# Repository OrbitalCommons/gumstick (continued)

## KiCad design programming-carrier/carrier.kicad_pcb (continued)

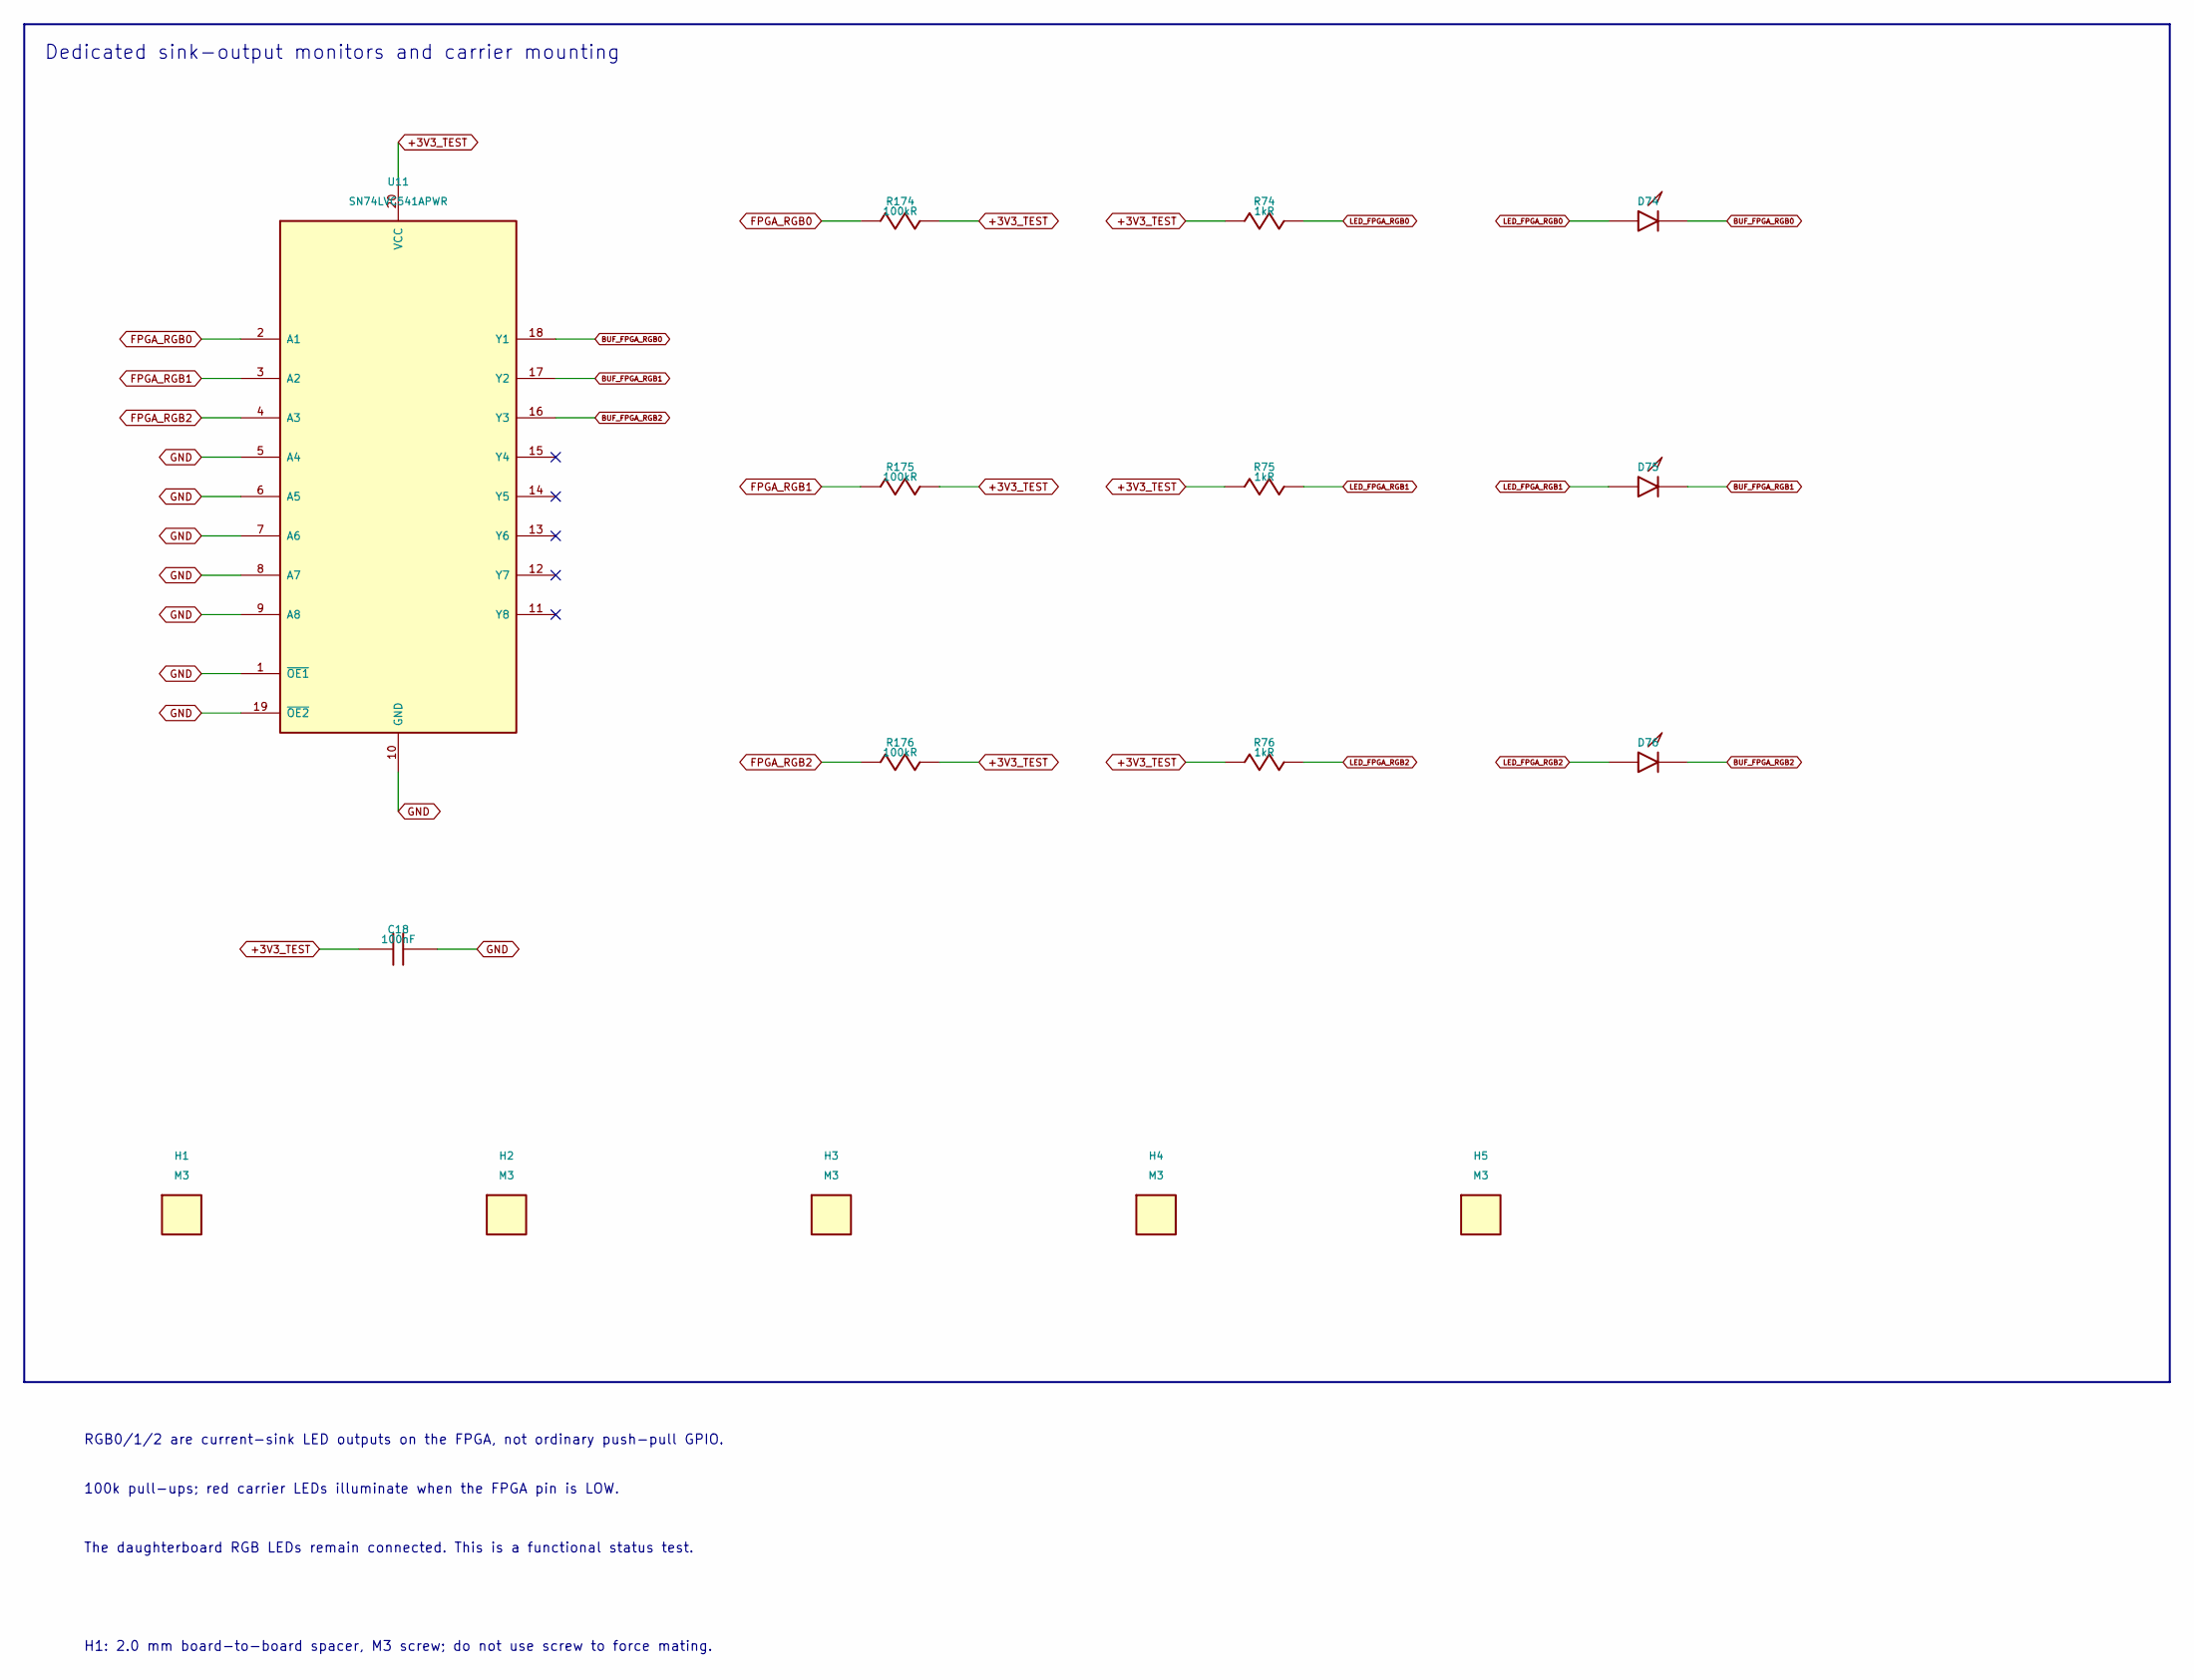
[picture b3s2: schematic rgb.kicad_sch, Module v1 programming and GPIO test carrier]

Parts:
C18: 100nF; C_0603_1608Metric; MPN CC0603KRX7R9BB104; LCSC C14663
D74, D75, D76: RED; LED_0603_1608Metric; MPN KT-0603R; LCSC C2286
H1, H2, H3, H4, H5: M3; MountingHole_3.2mm_M3; MPN M3
R74, R75, R76: 1kR; R_0603_1608Metric; MPN 0603WAF1001T5E; LCSC C21190
R174, R175, R176: 100kR; R_0603_1608Metric; MPN 0603WAF1003T5E; LCSC C25803
U11: SN74LVC541APWR; TSSOP-20_4.4x6.5mm_P0.65mm; MPN SN74LVC541APWR; LCSC C113281

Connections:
+3V3_TEST: C18.1, R74.1, R75.1, R76.1, R174.2, R175.2, R176.2, U11.20 (VCC); also elsewhere on the board
BUF_FPGA_RGB0: D74.1, U11.18 (Y1)
BUF_FPGA_RGB1: D75.1, U11.17 (Y2)
BUF_FPGA_RGB2: D76.1, U11.16 (Y3)
FPGA_RGB0: R174.1, U11.2 (A1); also elsewhere on the board
FPGA_RGB1: R175.1, U11.3 (A2); also elsewhere on the board
FPGA_RGB2: R176.1, U11.4 (A3); also elsewhere on the board
GND: C18.2, U11.1 (~OE1), U11.5 (A4), U11.6 (A5), U11.7 (A6), U11.8 (A7), U11.9 (A8), U11.10 (GND), U11.19 (~OE2); also elsewhere on the board
LED_FPGA_RGB0: D74.2, R74.2
LED_FPGA_RGB1: D75.2, R75.2
LED_FPGA_RGB2: D76.2, R76.2

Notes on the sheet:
Dedicated sink-output monitors and carrier mounting
RGB0/1/2 are current-sink LED outputs on the FPGA, not ordinary push-pull GPIO.
100k pull-ups; red carrier LEDs illuminate when the FPGA pin is LOW.
The daughterboard RGB LEDs remain connected. This is a functional status test.
H1: 2.0 mm board-to-board spacer, M3 screw; do not use screw to force mating.

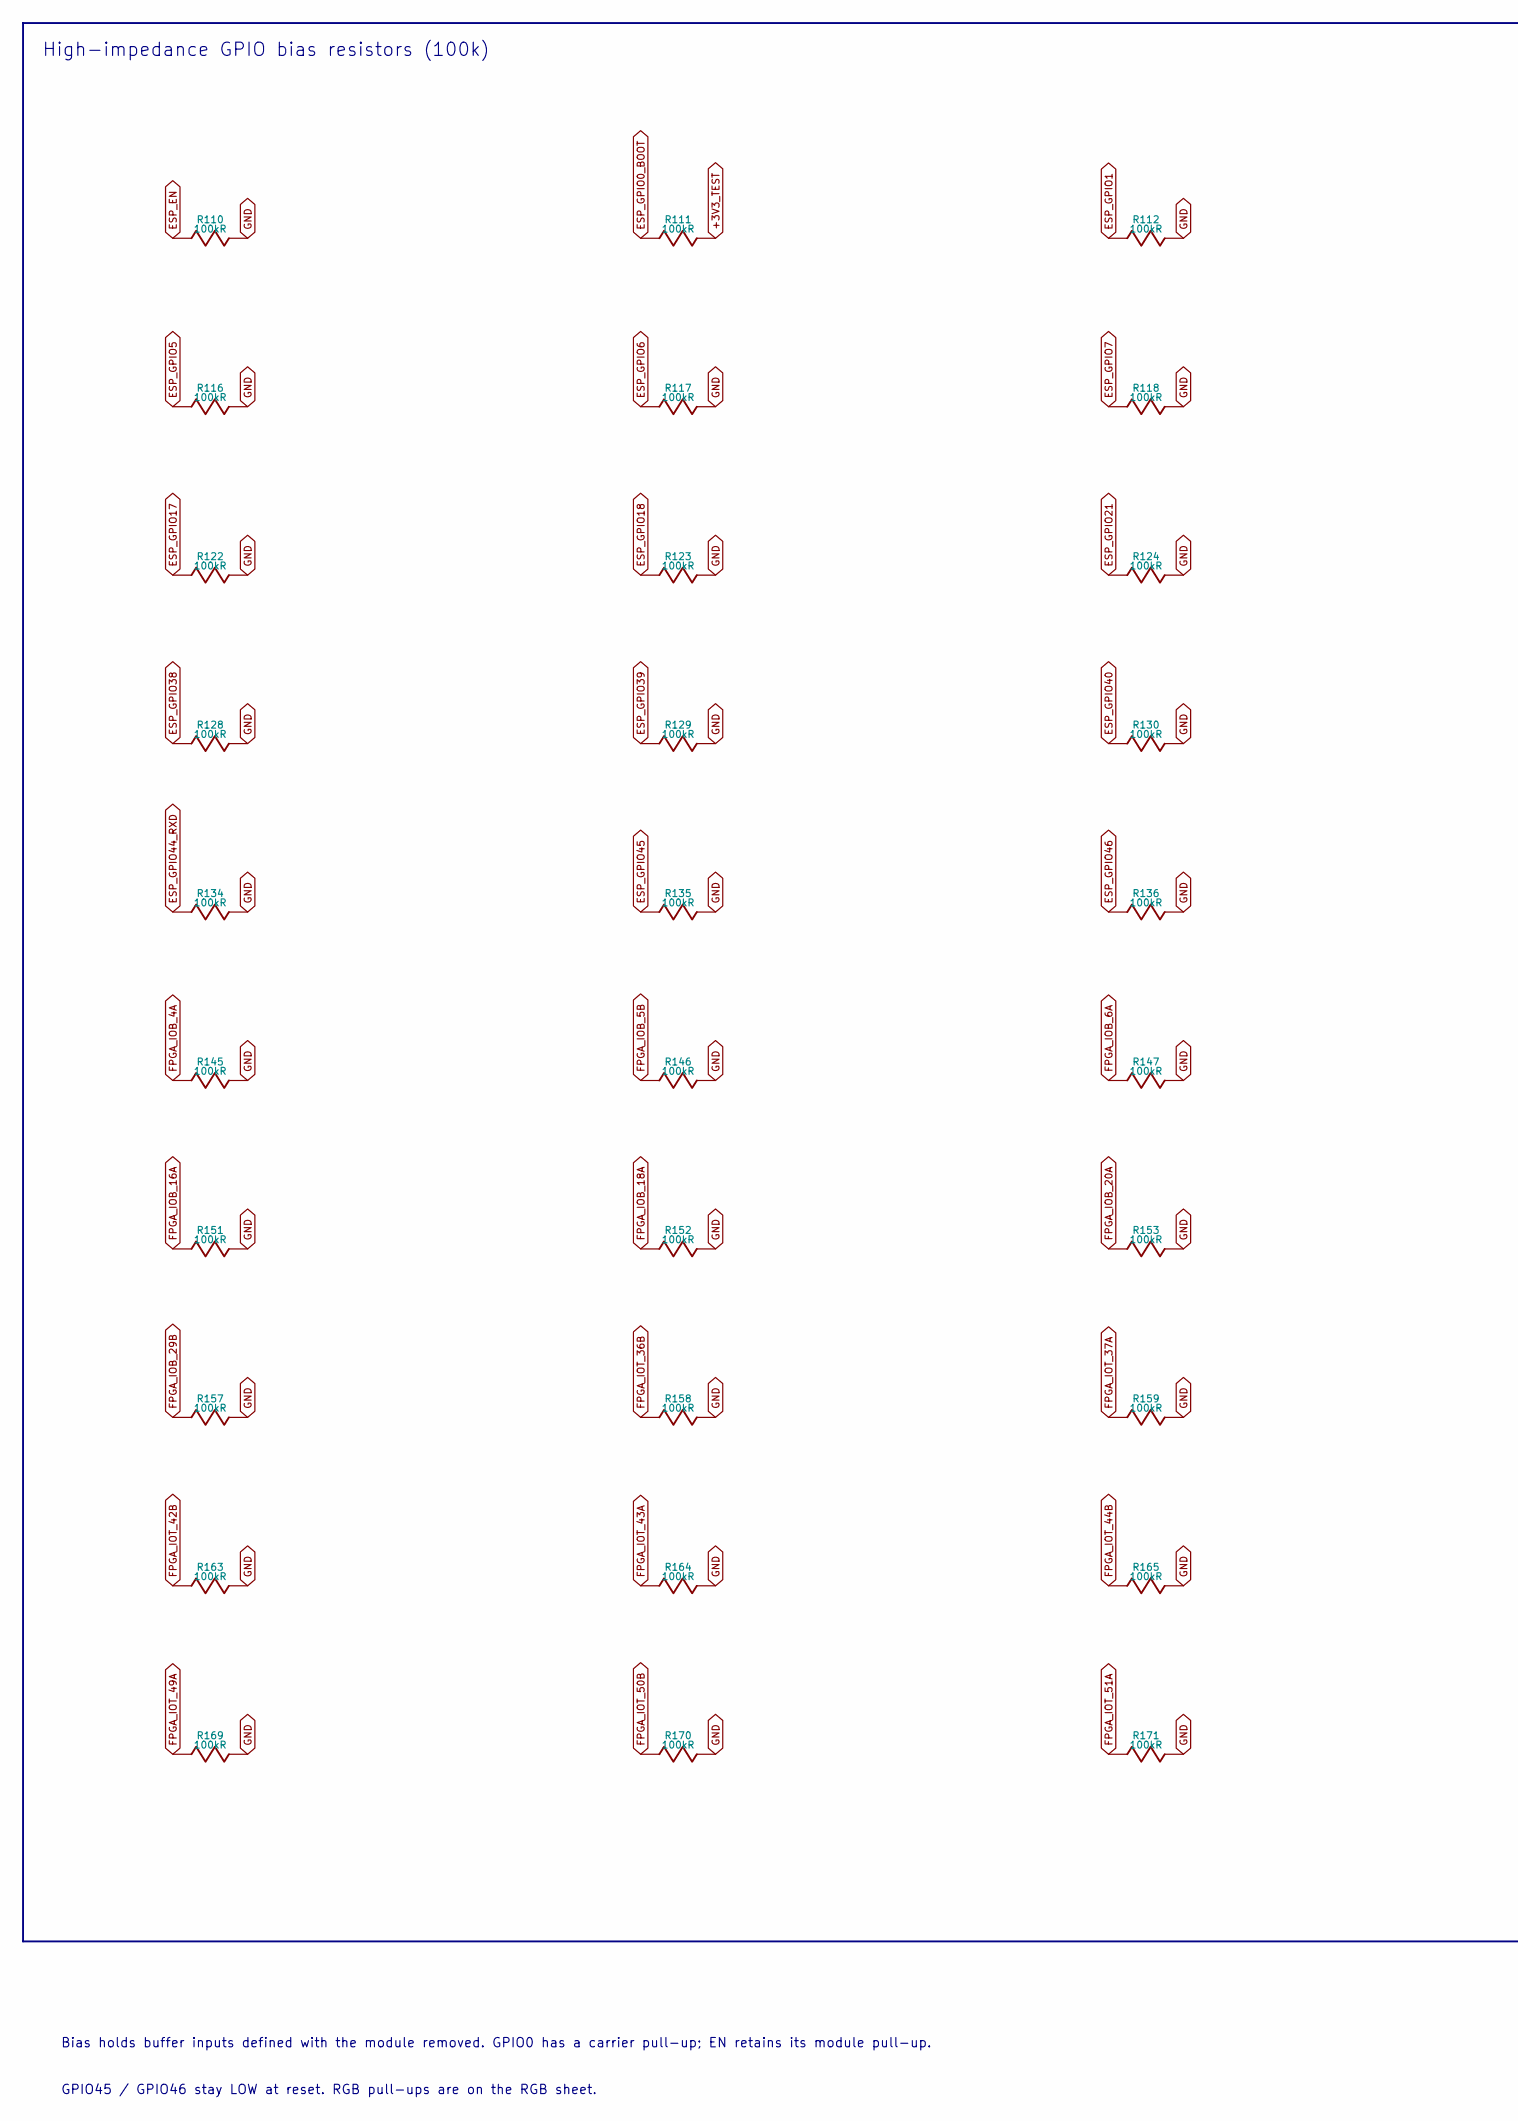
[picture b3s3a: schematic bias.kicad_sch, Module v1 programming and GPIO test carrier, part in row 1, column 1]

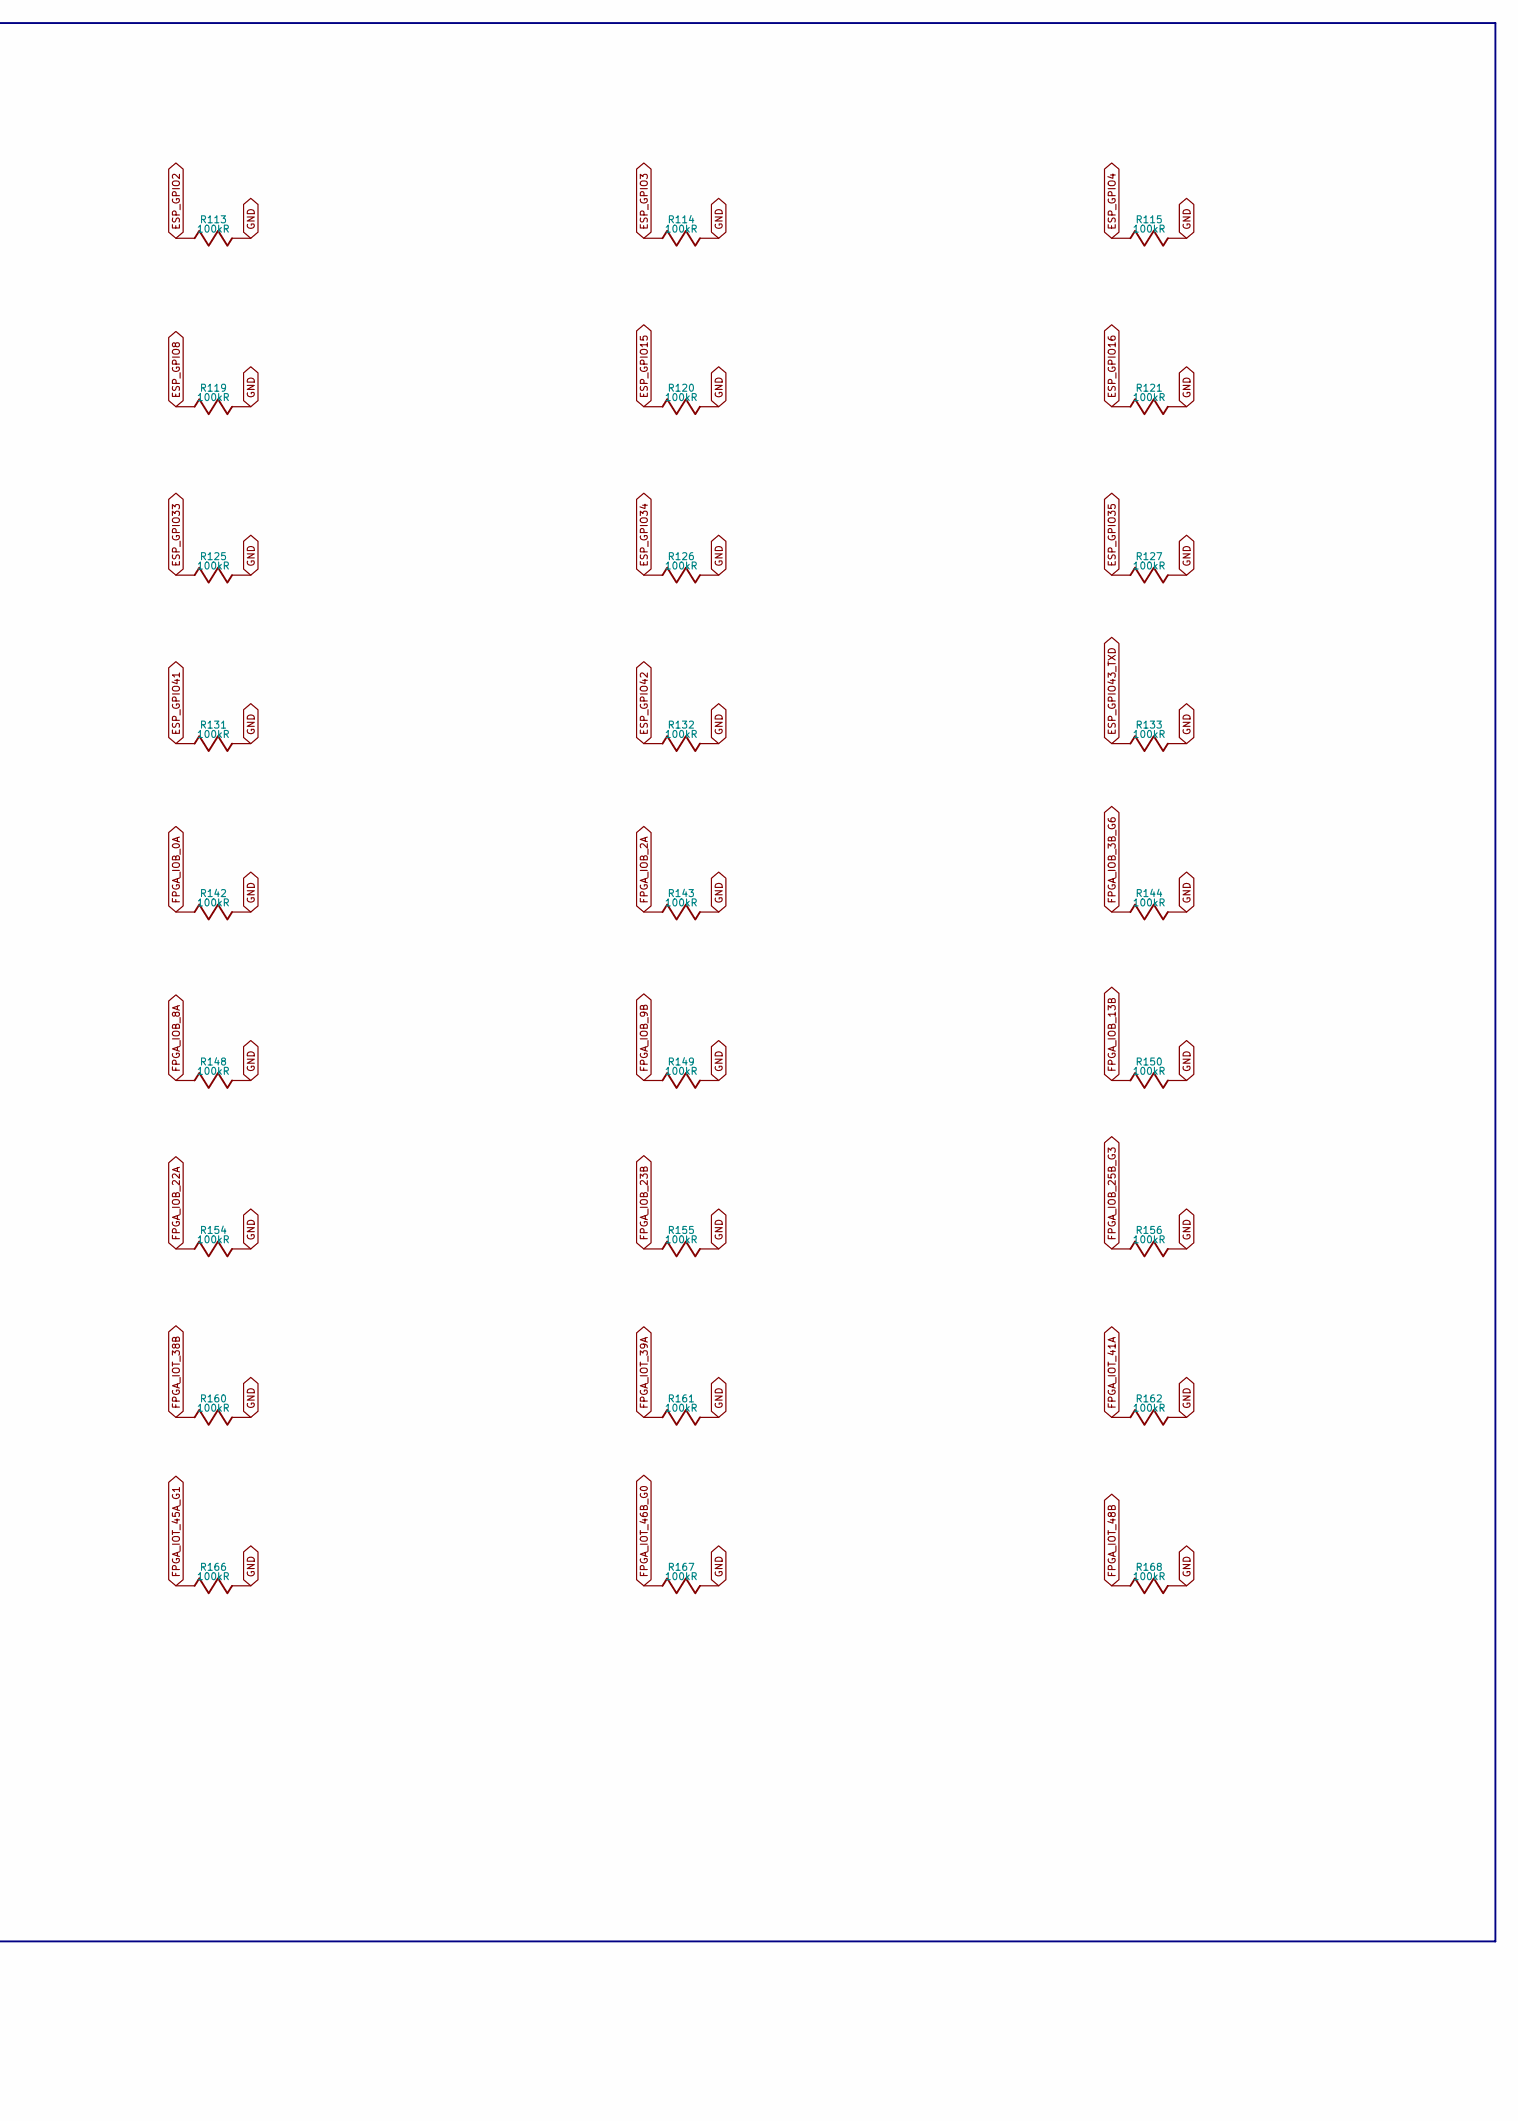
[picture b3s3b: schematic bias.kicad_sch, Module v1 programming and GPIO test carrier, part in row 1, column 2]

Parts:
R110, R111, R112, R113, R114, R115, R116, R117, R118, R119, R120, R121, R122, R123, R124, R125, R126, R127, R128, R129, R130, R131, R132, R133, R134, R135, R136, R142, R143, R144, R145, R146, R147, R148, R149, R150, R151, R152, R153, R154, R155, R156, R157, R158, R159, R160, R161, R162, R163, R164, R165, R166, R167, R168, R169, R170, R171: 100kR; R_0603_1608Metric; MPN 0603WAF1003T5E; LCSC C25803

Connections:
+3V3_TEST: R111.2; also elsewhere on the board
ESP_EN: R110.1; also elsewhere on the board
ESP_GPIO0_BOOT: R111.1; also elsewhere on the board
ESP_GPIO1: R112.1; also elsewhere on the board
ESP_GPIO2: R113.1; also elsewhere on the board
ESP_GPIO3: R114.1; also elsewhere on the board
ESP_GPIO4: R115.1; also elsewhere on the board
ESP_GPIO5: R116.1; also elsewhere on the board
ESP_GPIO6: R117.1; also elsewhere on the board
ESP_GPIO7: R118.1; also elsewhere on the board
ESP_GPIO8: R119.1; also elsewhere on the board
ESP_GPIO15: R120.1; also elsewhere on the board
ESP_GPIO16: R121.1; also elsewhere on the board
ESP_GPIO17: R122.1; also elsewhere on the board
ESP_GPIO18: R123.1; also elsewhere on the board
ESP_GPIO21: R124.1; also elsewhere on the board
ESP_GPIO33: R125.1; also elsewhere on the board
ESP_GPIO34: R126.1; also elsewhere on the board
ESP_GPIO35: R127.1; also elsewhere on the board
ESP_GPIO38: R128.1; also elsewhere on the board
ESP_GPIO39: R129.1; also elsewhere on the board
ESP_GPIO40: R130.1; also elsewhere on the board
ESP_GPIO41: R131.1; also elsewhere on the board
ESP_GPIO42: R132.1; also elsewhere on the board
ESP_GPIO43_TXD: R133.1; also elsewhere on the board
ESP_GPIO44_RXD: R134.1; also elsewhere on the board
ESP_GPIO45: R135.1; also elsewhere on the board
ESP_GPIO46: R136.1; also elsewhere on the board
FPGA_IOB_0A: R142.1; also elsewhere on the board
FPGA_IOB_2A: R143.1; also elsewhere on the board
FPGA_IOB_3B_G6: R144.1; also elsewhere on the board
FPGA_IOB_4A: R145.1; also elsewhere on the board
FPGA_IOB_5B: R146.1; also elsewhere on the board
FPGA_IOB_6A: R147.1; also elsewhere on the board
FPGA_IOB_8A: R148.1; also elsewhere on the board
FPGA_IOB_9B: R149.1; also elsewhere on the board
FPGA_IOB_13B: R150.1; also elsewhere on the board
FPGA_IOB_16A: R151.1; also elsewhere on the board
FPGA_IOB_18A: R152.1; also elsewhere on the board
FPGA_IOB_20A: R153.1; also elsewhere on the board
FPGA_IOB_22A: R154.1; also elsewhere on the board
FPGA_IOB_23B: R155.1; also elsewhere on the board
FPGA_IOB_25B_G3: R156.1; also elsewhere on the board
FPGA_IOB_29B: R157.1; also elsewhere on the board
FPGA_IOT_36B: R158.1; also elsewhere on the board
FPGA_IOT_37A: R159.1; also elsewhere on the board
FPGA_IOT_38B: R160.1; also elsewhere on the board
FPGA_IOT_39A: R161.1; also elsewhere on the board
FPGA_IOT_41A: R162.1; also elsewhere on the board
FPGA_IOT_42B: R163.1; also elsewhere on the board
FPGA_IOT_43A: R164.1; also elsewhere on the board
FPGA_IOT_44B: R165.1; also elsewhere on the board
FPGA_IOT_45A_G1: R166.1; also elsewhere on the board
FPGA_IOT_46B_G0: R167.1; also elsewhere on the board
FPGA_IOT_48B: R168.1; also elsewhere on the board
FPGA_IOT_49A: R169.1; also elsewhere on the board
FPGA_IOT_50B: R170.1; also elsewhere on the board
FPGA_IOT_51A: R171.1; also elsewhere on the board
GND: R110.2, R112.2, R113.2, R114.2, R115.2, R116.2, R117.2, R118.2, R119.2, R120.2, R121.2, R122.2, R123.2, R124.2, R125.2, R126.2, R127.2, R128.2, R129.2, R130.2, R131.2, R132.2, R133.2, R134.2, R135.2, R136.2, R142.2, R143.2, R144.2, R145.2, R146.2, R147.2, R148.2, R149.2, R150.2, R151.2, R152.2, R153.2, R154.2, R155.2, R156.2, R157.2, R158.2, R159.2, R160.2, R161.2, R162.2, R163.2, R164.2, R165.2, R166.2, R167.2, R168.2, R169.2, R170.2, R171.2; also elsewhere on the board

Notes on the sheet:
High-impedance GPIO bias resistors (100k)
Bias holds buffer inputs defined with the module removed. GPIO0 has a carrier pull-up; EN retains its module pull-up.
GPIO45 / GPIO46 stay LOW at reset. RGB pull-ups are on the RGB sheet.

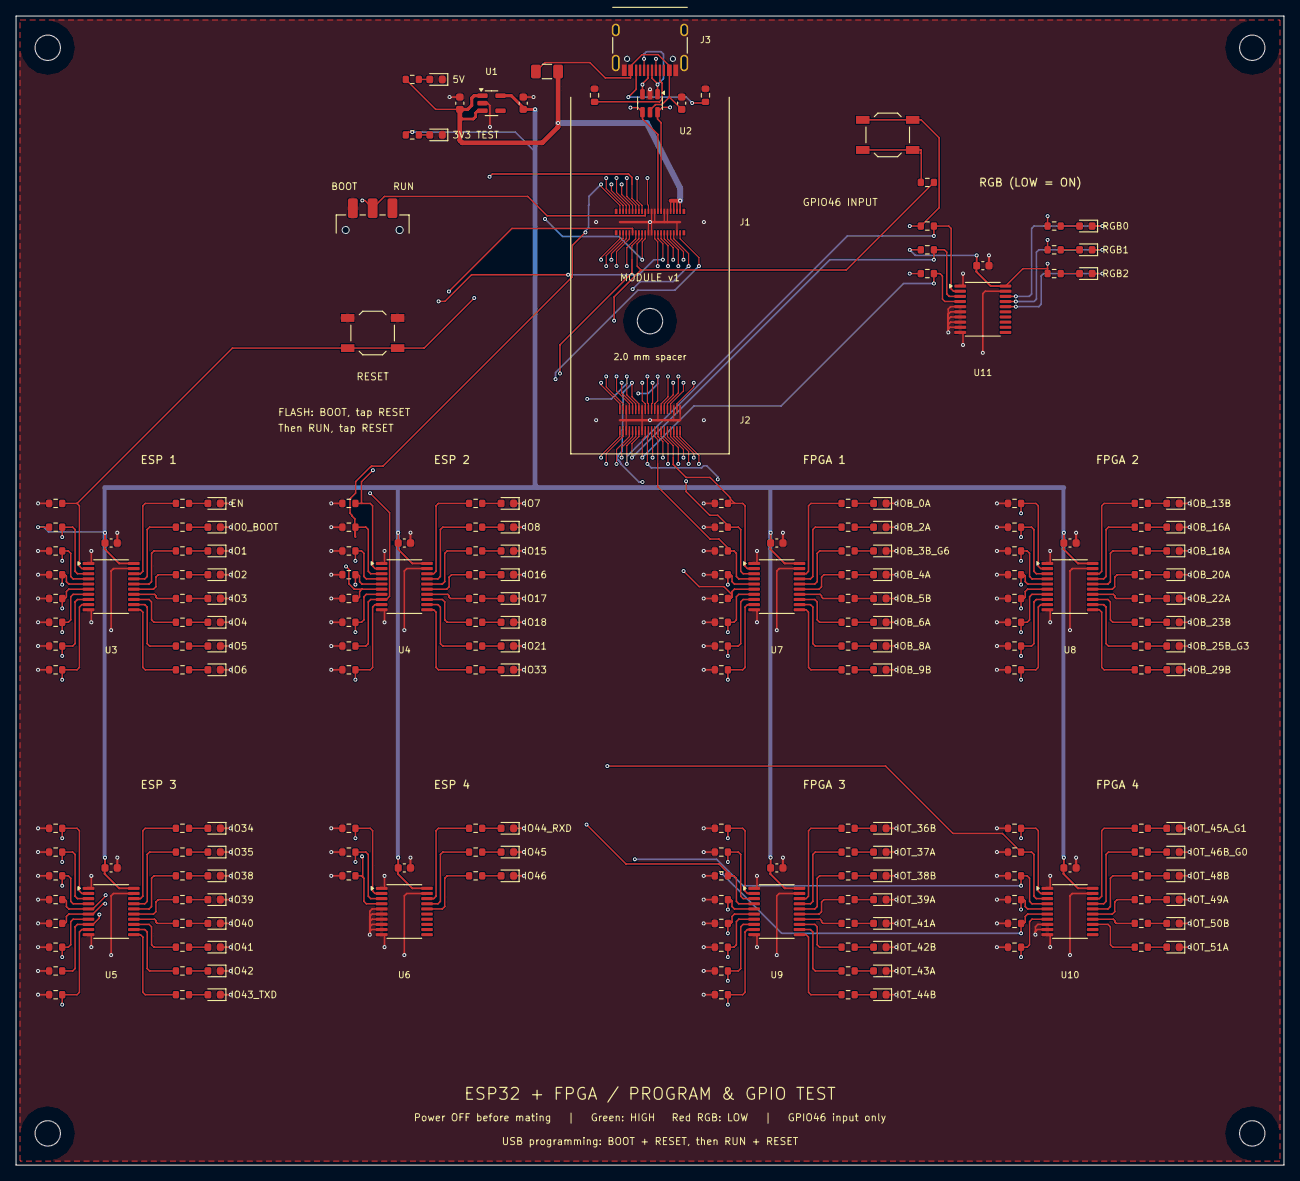
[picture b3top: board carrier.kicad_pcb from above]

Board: 4 copper layers, 160.0 x 145.0 mm, 222 parts (0 on the bottom side), 191 nets.

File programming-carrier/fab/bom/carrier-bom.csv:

Comment,Designator,Quantity,Footprint,MPN,LCSC Part #,Supplier URL
4.7uF,"C1,C2",2,Carrier:C_0603_1608Metric,CL10A475KO8NNNC,C19666,https://www.lcsc.com/product-detail/C19666.html
100nF,"C3,C10,C11,C12,C13,C14,C15,C16,C17,C18",10,Carrier:C_0603_1608Metric,CC0603KRX7R9BB104,C14663,https://www.lcsc.com/product-detail/C14663.html
GREEN,"D1,D2,D10,D11,D12,D13,D14,D15,D16,D17,D18,D19,D20,D21,D22,D23,D24,D25,D26,D27,D28,D29,D30,D31,D32,D33,D34,D35,D36,D42,D43,D44,D45,D46,D47,D48,D49,D50,D51,D52,D53,D54,D55,D56,D57,D58,D59,D60,D61,D62,D63,D64,D65,D66,D67,D68,D69,D70,D71",59,Carrier:LED_0603_1608Metric,XL-1608SYGC-06,C965805,https://www.lcsc.com/product-detail/C965805.html
RED,"D74,D75,D76",3,Carrier:LED_0603_1608Metric,KT-0603R,C2286,https://www.lcsc.com/product-detail/C2286.html
500mA PTC,F1,1,Carrier:Fuse_1206_3216Metric,1206L050/15YR,C151162,https://www.lcsc.com/product-detail/C151162.html
DF40C-40DP-0.4V(51),J1,1,Carrier:J1_Module_v1_Mate,DF40C-40DP-0.4V(51),C424643,https://www.lcsc.com/product-detail/C424643.html
DF40C(2.0)-40DS-0.4V(51),J2,1,Carrier:J2_Module_v1_Mate,DF40C(2.0)-40DS-0.4V(51),C597934,https://www.lcsc.com/product-detail/C597934.html
USB-C USB2,J3,1,Carrier:USB_C_Receptacle_HRO_TYPE-C-31-M-12,TYPE-C-31-M-12,C165948,https://www.lcsc.com/product-detail/C165948.html
5.1kR,"R1,R2",2,Carrier:R_0603_1608Metric,0603WAF5101T5E,C23186,https://www.lcsc.com/product-detail/C23186.html
2.2kR,R3,1,Carrier:R_0603_1608Metric,0603WAF2201T5E,C4190,https://www.lcsc.com/product-detail/C4190.html
1kR,"R4,R5,R10,R11,R12,R13,R14,R15,R16,R17,R18,R19,R20,R21,R22,R23,R24,R25,R26,R27,R28,R29,R30,R31,R32,R33,R34,R35,R36,R42,R43,R44,R45,R46,R47,R48,R49,R50,R51,R52,R53,R54,R55,R56,R57,R58,R59,R60,R61,R62,R63,R64,R65,R66,R67,R68,R69,R70,R71,R74,R75,R76",62,Carrier:R_0603_1608Metric,0603WAF1001T5E,C21190,https://www.lcsc.com/product-detail/C21190.html
100kR,"R110,R111,R112,R113,R114,R115,R116,R117,R118,R119,R120,R121,R122,R123,R124,R125,R126,R127,R128,R129,R130,R131,R132,R133,R134,R135,R136,R142,R143,R144,R145,R146,R147,R148,R149,R150,R151,R152,R153,R154,R155,R156,R157,R158,R159,R160,R161,R162,R163,R164,R165,R166,R167,R168,R169,R170,R171,R174,R175,R176",60,Carrier:R_0603_1608Metric,0603WAF1003T5E,C25803,https://www.lcsc.com/product-detail/C25803.html
BOOT / RUN,SW1,1,Carrier:SW_SPDT_CK_JS102011SAQN,JS102011SAQN,C221660,https://www.lcsc.com/product-detail/C221660.html
RESET / GPIO46 INPUT,"SW2,SW3",2,Carrier:SW_SPST_TL3342,TL3342F160QG,C2886898,https://www.lcsc.com/product-detail/C2886898.html
AP2112K-3.3,U1,1,Carrier:SOT-23-5,AP2112K-3.3TRG1,C51118,https://www.lcsc.com/product-detail/C51118.html
USBLC6-2SC6,U2,1,Carrier:SOT-23-6,USBLC6-2SC6,C7519,https://www.lcsc.com/product-detail/C7519.html
SN74LVC541APWR,"U3,U4,U5,U6,U7,U8,U9,U10,U11",9,Carrier:TSSOP-20_4.4x6.5mm_P0.65mm,SN74LVC541APWR,C113281,https://www.lcsc.com/product-detail/C113281.html
